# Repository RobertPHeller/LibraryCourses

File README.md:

# Library Courses

These are my course notes for courses I plan on teachibng at the Wendell Free 
Library. 

- [Scratch For Kids](https://github.com/RobertPHeller/LibraryCourses/tree/main/ScratchForKids)
  This is a course for school age kids (4th through 6th grade) teaching computer 
  programming using the Scratch programming environment.
- [Sonic Pi For All Ages](https://github.com/RobertPHeller/LibraryCourses/tree/main/SonicPiForAllAges)
  This is a course teaching Sonic Pi, which is a programming environment for 
  making music. This is an all-ages course.  
- [Arduino And Robotics For Kids](https://github.com/RobertPHeller/LibraryCourses/tree/main/ArduinoAndRoboticsForKids)
  A fun course learning about electronic circuits and robotics.

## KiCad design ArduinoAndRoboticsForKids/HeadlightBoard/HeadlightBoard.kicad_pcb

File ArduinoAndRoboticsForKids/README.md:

# Arduino And Robotics For Kids

A fun course learning about electronic circuits and robotics.

Text Book: TBA

- What is a robot?

  Different kinds of robots: Humanoid, like C3PO or Commander Data, quasi 
  humanoid robots like the robots from Lost In Space or The Forbidden Planet.
  Non-humanoid robots like R2D2 or Number 5. Robotic dogs from Boston 
  Dynamics.  iRobot Roomba. Non-mobile industrial robots. (Pictures!)

  - 
  - 
  - 
  - 
  - 
  - 
  - 
  - 
  - 
  
  How robots work. Motors for muscles. Sensors to help robots "see". Micro
  Processors for brains. Batteries to give robots the energy to operate.
  
- Arduino and Electronics

  -  LEDs and resistors: Blink a LED.
  -  Operating a servo for precise movement.
  -  Transistors and Motors: using a transistor to do the heavy lifting.
  -  LDRs to sense how bright it is.
  -  Using sound to navigate like a bat: using an ultrasonic sensor to measure 
  distance. 

- Assembling a wheeled platform for our robot

  Writing programs to control moving around: forwards and backwards, 
    turning left and right.
    
- Adding ultrasonic sensors to our wheeled platform

  Avoiding crashes into walls and obstacles.
  
- Adding a gripper to our robot.

  Picking things up and carrying them around and putting them down.

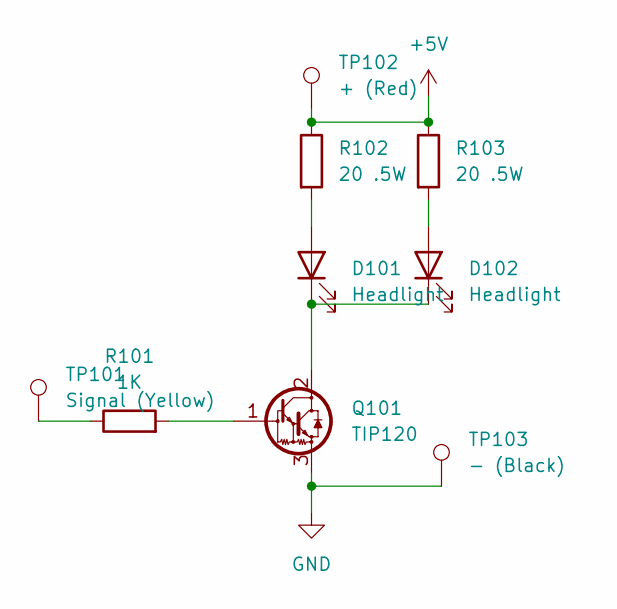
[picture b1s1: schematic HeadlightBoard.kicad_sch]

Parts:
D101, D102: Headlight; DS203; Mouser Part Number 997-L1356580CA350P1
Q101: TIP120; TO-220-3_Vertical
R101: 1K; R_0805_2012Metric; Mouser Part Number 603-RC0805JR-101KL
R102, R103: 20 .5W; R_1210_3225Metric; Mouser Part Number 652-CR2010-FX20R0ELF
TP101: Signal (Yellow); TestPoint_Plated_Hole_D2.0mm
TP102: + (Red); TestPoint_Plated_Hole_D2.0mm
TP103: - (Black); TestPoint_Plated_Hole_D2.0mm

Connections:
+5V: R102.1, R103.1, TP102.1
GND: Q101.3 (E), TP103.1
unnamed: D101.1 (K), D102.1 (K), Q101.2 (C)
unnamed: D101.2 (A), R102.2
unnamed: D102.2 (A), R103.2
unnamed: Q101.1 (B), R101.2
unnamed: R101.1, TP101.1

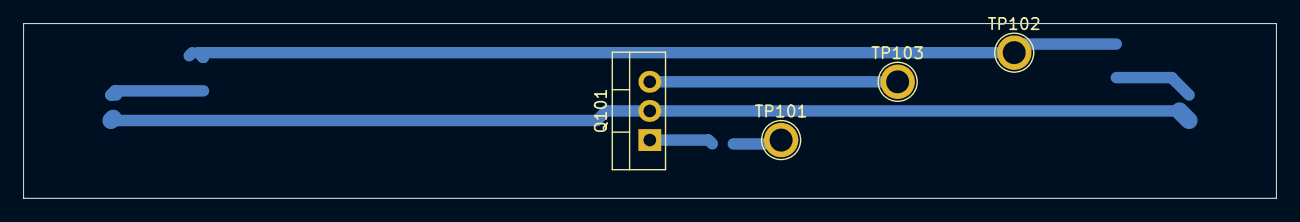
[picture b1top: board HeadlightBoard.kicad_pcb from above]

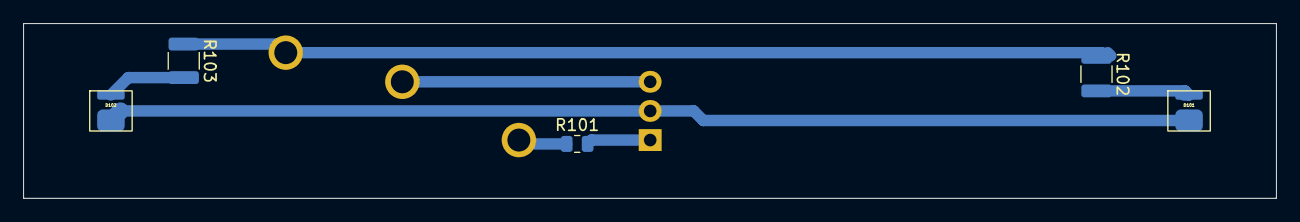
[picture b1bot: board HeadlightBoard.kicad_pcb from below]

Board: 2 copper layers, 109.2 x 15.2 mm, 9 parts (5 on the bottom side), 7 nets.

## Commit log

2024-02-03 Complete root README.
2024-02-03 Update links.
2024-02-03 Complete draft of the Scratch For Kids README.
2024-02-04 Complete draft the Sonic Pi For All Ages README.
2024-02-04 Started Arduino And Robotics For Kids README.
2024-02-04 Arduino And Robotics For Kids README.
2024-02-05 Arduino And Robotics For Kids
2024-02-06 Add .gitignore.
2024-02-06 Add License.
2024-02-06 Add Chapter 1 project.
2024-02-06 Add project: LED-and-resistor-UNO and Blink.
2024-02-07 Add Arduino circuit projects.
2024-02-07 Normalize Arduino and Fritzing file names.
2024-02-07 Minor updates.
2024-02-07 Update LEDSAndResistors to use a breadboard. Add Transistor-and-motor.
2024-02-07 Add UltraSonic.
2024-02-07 Update UltraSonic to SRF05.
2024-02-07 Add robot docs.
2024-02-07 Add RoMeo schematic (1.1).
2024-02-07 Update UntraSonic to use SRF05 with one pin.
2024-02-08 Add LDR Pdfs.
2024-02-08 Add TIP120 and LED Datasheets.
2024-02-08 Remove high voltage LED.
2024-02-08 Add LED Datasheet.
2024-02-08 Add 3D model of robot chassis.
2024-02-08 Add Robot I/O Map.
2024-02-09 Create Headlight Board.
2024-02-09 Start on Headlight Casing.
2024-02-09 Add dims to PCB.
2024-02-17 Add FrontHeadlightCasing and STL generators.
2024-02-18 Add MotorTest.
2024-02-25 Add Robot Parts List.
2024-03-03 Add Hand class and test program.
2024-09-12 Update UltraSonic test for SR04s. Create BounceOffWall demo program.
2024-09-14 Update BounceOffWall demo program.
2024-09-14 Add IRrecvDemo.
2024-09-18 Tweaks to BounceOffWall.
2024-09-20 Generic Robot program.
2024-09-26 Add GenericRobot.
2024-09-26 Update parts list.
2024-09-26 Add RobotCommandLanguage.
2024-09-27 Flesh out RCL.
2024-09-27 Add RCL_Shield.
2024-09-29 Test support for ESP32S3 RoMeo board.
2024-09-29 Update Makefile: set build.path preference.
2024-09-29 Add config.h.
